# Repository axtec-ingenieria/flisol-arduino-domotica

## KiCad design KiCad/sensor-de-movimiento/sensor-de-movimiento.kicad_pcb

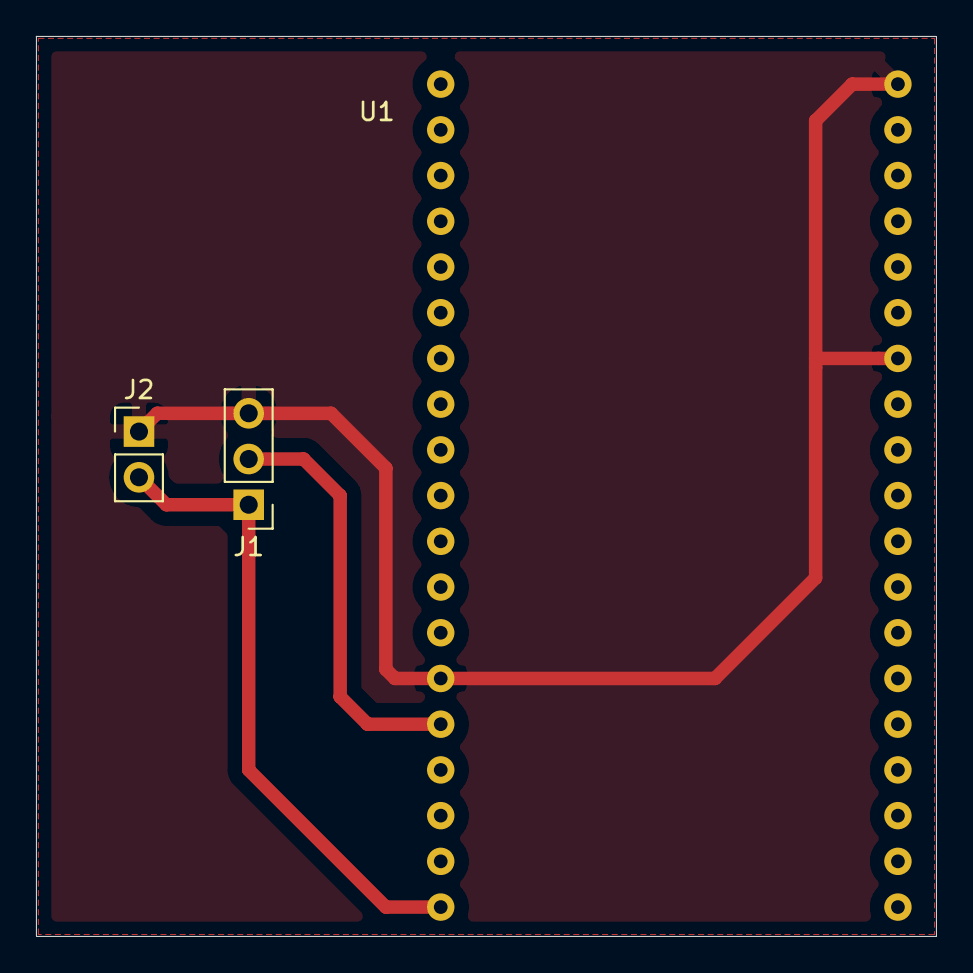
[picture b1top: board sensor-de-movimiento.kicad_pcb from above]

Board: 2 copper layers, 50.0 x 50.0 mm, 3 parts (0 on the bottom side), 3 nets.

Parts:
J1: Conector PIR; PinHeader_1x03_P2.54mm_Vertical
J2: Conector Bateria; PinHeader_1x02_P2.54mm_Vertical
U1: NodeMCU-32S; NodeMCU-ESP32

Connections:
+BATT: J1.1, J2.2, U1.19
GND: J1.3, J2.1, U1.14, U1.32, U1.38
unnamed: J1.2, U1.15

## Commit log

2019-04-27 Programa del servidor web en Arduino para ESP32
2019-04-27 Archivos KiCad para el PCB
2019-04-27 Diagrama de conexión en Fritzing
2019-04-27 Errores en KiCad
